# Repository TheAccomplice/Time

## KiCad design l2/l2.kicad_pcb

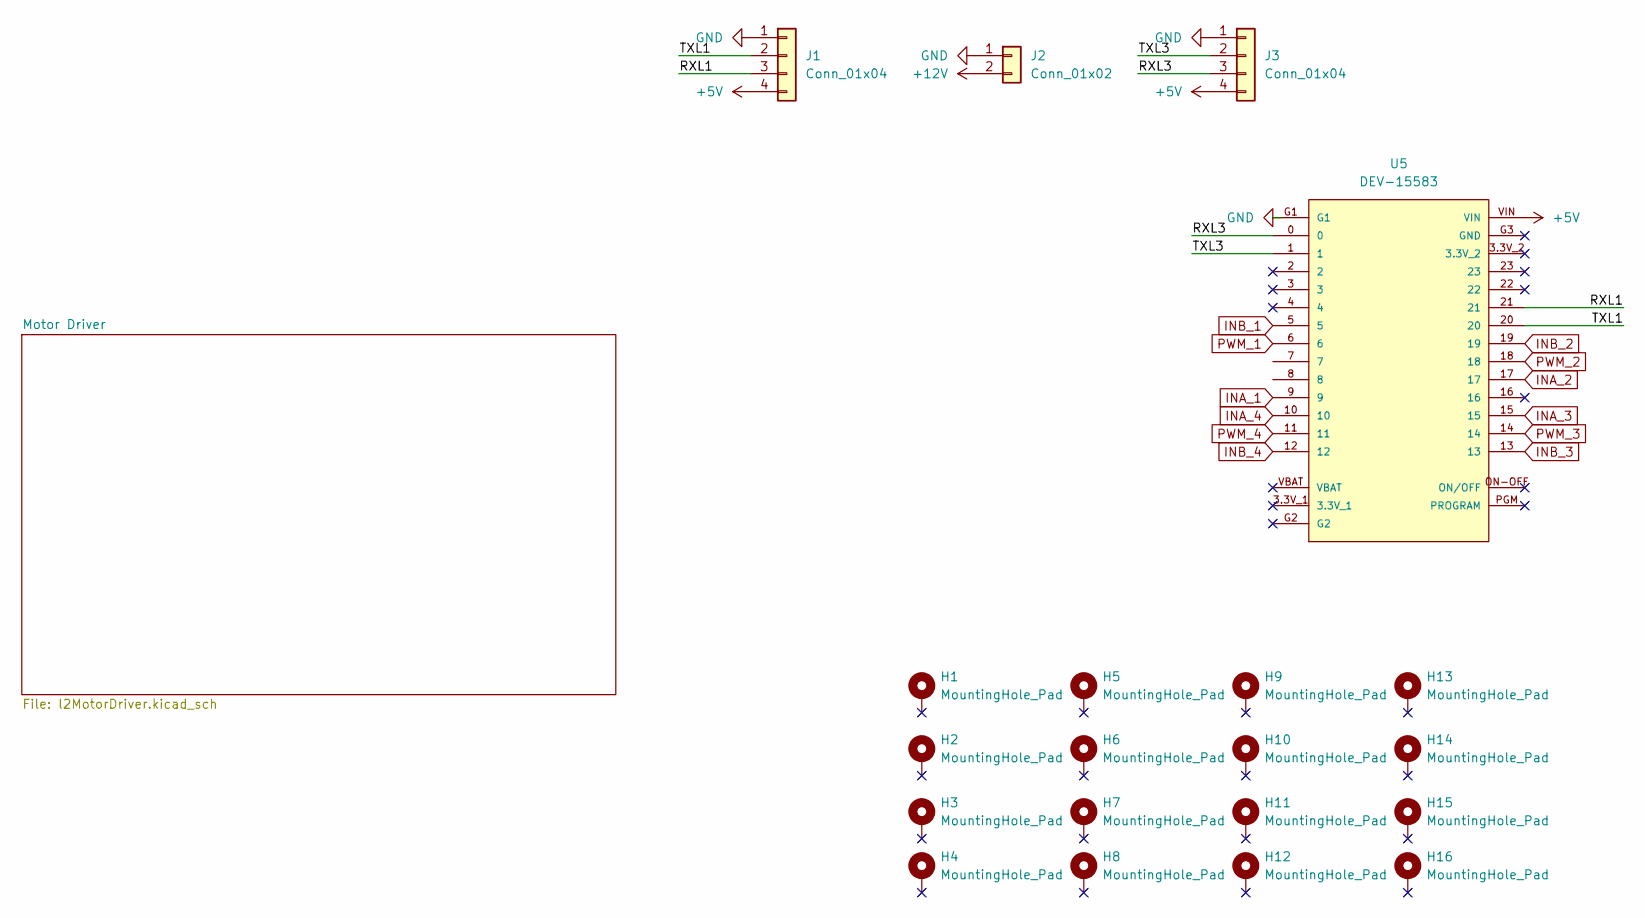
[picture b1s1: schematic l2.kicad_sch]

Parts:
H1, H2, H3, H4, H5, H6, H7, H8, H9, H10, H11, H12, H13, H14, H15, H16: MountingHole_Pad; MountingHole_3.2mm_M3_Pad_Via
J1, J3: Conn_01x04; JST_XH_B4B-XH-AM_1x04_P2.50mm_Vertical
J2: Conn_01x02; AMASS_XT60-M_1x02_P7.20mm_Vertical
U5: DEV-15583; MODULE_DEV-15583

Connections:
+5V: J1.4, J3.4, U5.VIN; also elsewhere on the board
+12V: J2.2; also elsewhere on the board
/RXL1: J1.3, U5.21
/RXL3: J3.3, U5.0
/TXL1: J1.2, U5.20
/TXL3: J3.2, U5.1
GND: J1.1, J2.1, J3.1, U5.G1; also elsewhere on the board
INA_1: U5.9; also elsewhere on the board
INA_2: U5.17; also elsewhere on the board
INA_3: U5.15; also elsewhere on the board
INA_4: U5.10; also elsewhere on the board
INB_1: U5.5; also elsewhere on the board
INB_2: U5.19; also elsewhere on the board
INB_3: U5.13; also elsewhere on the board
INB_4: U5.12; also elsewhere on the board
PWM_1: U5.6; also elsewhere on the board
PWM_2: U5.18; also elsewhere on the board
PWM_3: U5.14; also elsewhere on the board
PWM_4: U5.11; also elsewhere on the board

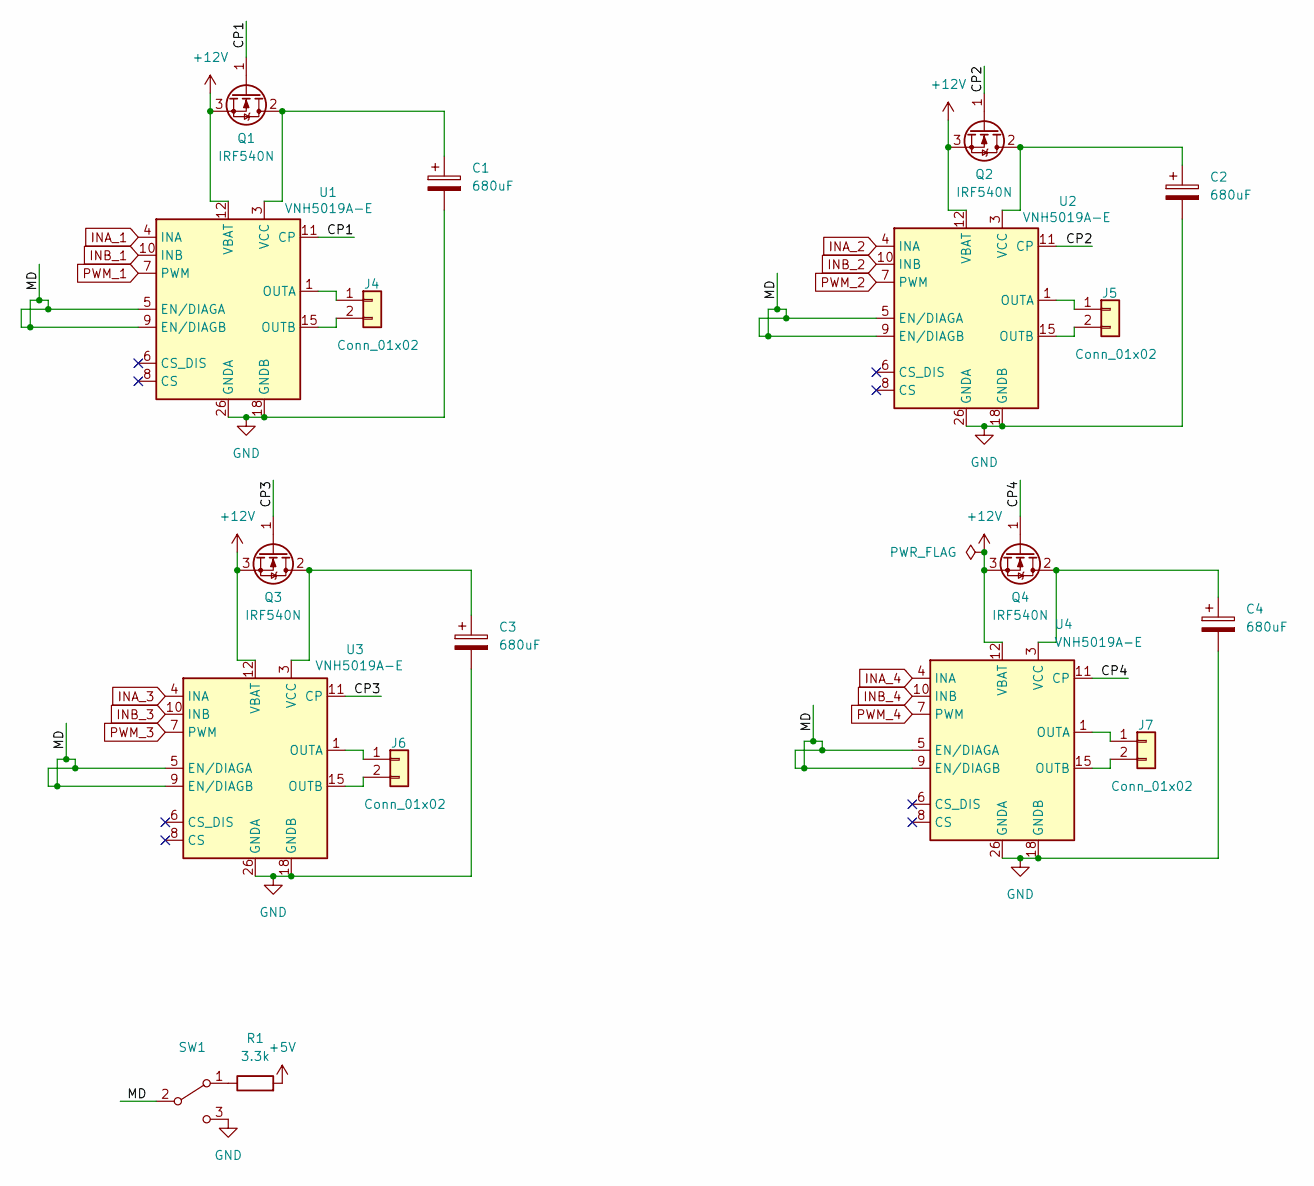
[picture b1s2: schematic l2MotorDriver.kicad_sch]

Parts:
C1, C2, C3, C4: 680uF; CP_Radial_D8.0mm_P3.50mm
J4, J5, J6, J7: Conn_01x02; AMASS_XT30UPB-F_1x02_P5.0mm_Vertical
Q1, Q2, Q3, Q4: IRF540N; TO-220-3_Vertical
R1: 3.3k; R_0603_1608Metric_Pad0.98x0.95mm_HandSolder
SW1: SW_SPDT; JST_XH_B3B-XH-AM_1x03_P2.50mm_Vertical
U1, U2, U3, U4: VNH5019A-E; VNH5019A-E_SO-30

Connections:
+5V: R1.2; also elsewhere on the board
+12V: Q1.3 (S), Q2.3 (S), Q3.3 (S), Q4.3 (S), U1.12 (VBAT), U2.12 (VBAT), U3.12 (VBAT), U4.12 (VBAT); also elsewhere on the board
/Motor Driver/CP1: Q1.1 (G), U1.11 (CP)
/Motor Driver/CP2: Q2.1 (G), U2.11 (CP)
/Motor Driver/CP3: Q3.1 (G), U3.11 (CP)
/Motor Driver/CP4: Q4.1 (G), U4.11 (CP)
/Motor Driver/MD: SW1.2 (B), U1.5 (EN/DIAGA), U1.9 (EN/DIAGB), U2.5 (EN/DIAGA), U2.9 (EN/DIAGB), U3.5 (EN/DIAGA), U3.9 (EN/DIAGB), U4.5 (EN/DIAGA), U4.9 (EN/DIAGB)
GND: C1.2, C2.2, C3.2, C4.2, SW1.3 (C), U1.18 (GNDB), U1.19 (GNDB), U1.20 (GNDB), U1.26 (GNDA), U1.27 (GNDA), U1.28 (GNDA), U2.18 (GNDB), U2.19 (GNDB), U2.20 (GNDB), U2.26 (GNDA), U2.27 (GNDA), U2.28 (GNDA), U3.18 (GNDB), U3.19 (GNDB), U3.20 (GNDB), U3.26 (GNDA), U3.27 (GNDA), U3.28 (GNDA), U4.18 (GNDB), U4.19 (GNDB), U4.20 (GNDB), U4.26 (GNDA), U4.27 (GNDA), U4.28 (GNDA); also elsewhere on the board
INA_1: U1.4 (INA); also elsewhere on the board
INA_2: U2.4 (INA); also elsewhere on the board
INA_3: U3.4 (INA); also elsewhere on the board
INA_4: U4.4 (INA); also elsewhere on the board
INB_1: U1.10 (INB); also elsewhere on the board
INB_2: U2.10 (INB); also elsewhere on the board
INB_3: U3.10 (INB); also elsewhere on the board
INB_4: U4.10 (INB); also elsewhere on the board
unnamed: J4.1, U1.1 (OUTA), U1.25 (OUTA), U1.30 (OUTA), U1.33 (OUTA)
unnamed: J4.2, U1.15 (OUTB), U1.16 (OUTB), U1.21 (OUTB), U1.32 (OUTB)
unnamed: J5.1, U2.1 (OUTA), U2.25 (OUTA), U2.30 (OUTA), U2.33 (OUTA)
unnamed: J5.2, U2.15 (OUTB), U2.16 (OUTB), U2.21 (OUTB), U2.32 (OUTB)
unnamed: J6.1, U3.1 (OUTA), U3.25 (OUTA), U3.30 (OUTA), U3.33 (OUTA)
unnamed: J6.2, U3.15 (OUTB), U3.16 (OUTB), U3.21 (OUTB), U3.32 (OUTB)
unnamed: J7.1, U4.1 (OUTA), U4.25 (OUTA), U4.30 (OUTA), U4.33 (OUTA)
unnamed: J7.2, U4.15 (OUTB), U4.16 (OUTB), U4.21 (OUTB), U4.32 (OUTB)
unnamed: C1.1, Q1.2 (D), U1.3 (VCC), U1.13 (VCC), U1.23 (VCC), U1.31 (VCC)
unnamed: C2.1, Q2.2 (D), U2.3 (VCC), U2.13 (VCC), U2.23 (VCC), U2.31 (VCC)
unnamed: C3.1, Q3.2 (D), U3.3 (VCC), U3.13 (VCC), U3.23 (VCC), U3.31 (VCC)
unnamed: C4.1, Q4.2 (D), U4.3 (VCC), U4.13 (VCC), U4.23 (VCC), U4.31 (VCC)
unnamed: R1.1, SW1.1 (A)
PWM_1: U1.7 (PWM); also elsewhere on the board
PWM_2: U2.7 (PWM); also elsewhere on the board
PWM_3: U3.7 (PWM); also elsewhere on the board
PWM_4: U4.7 (PWM); also elsewhere on the board

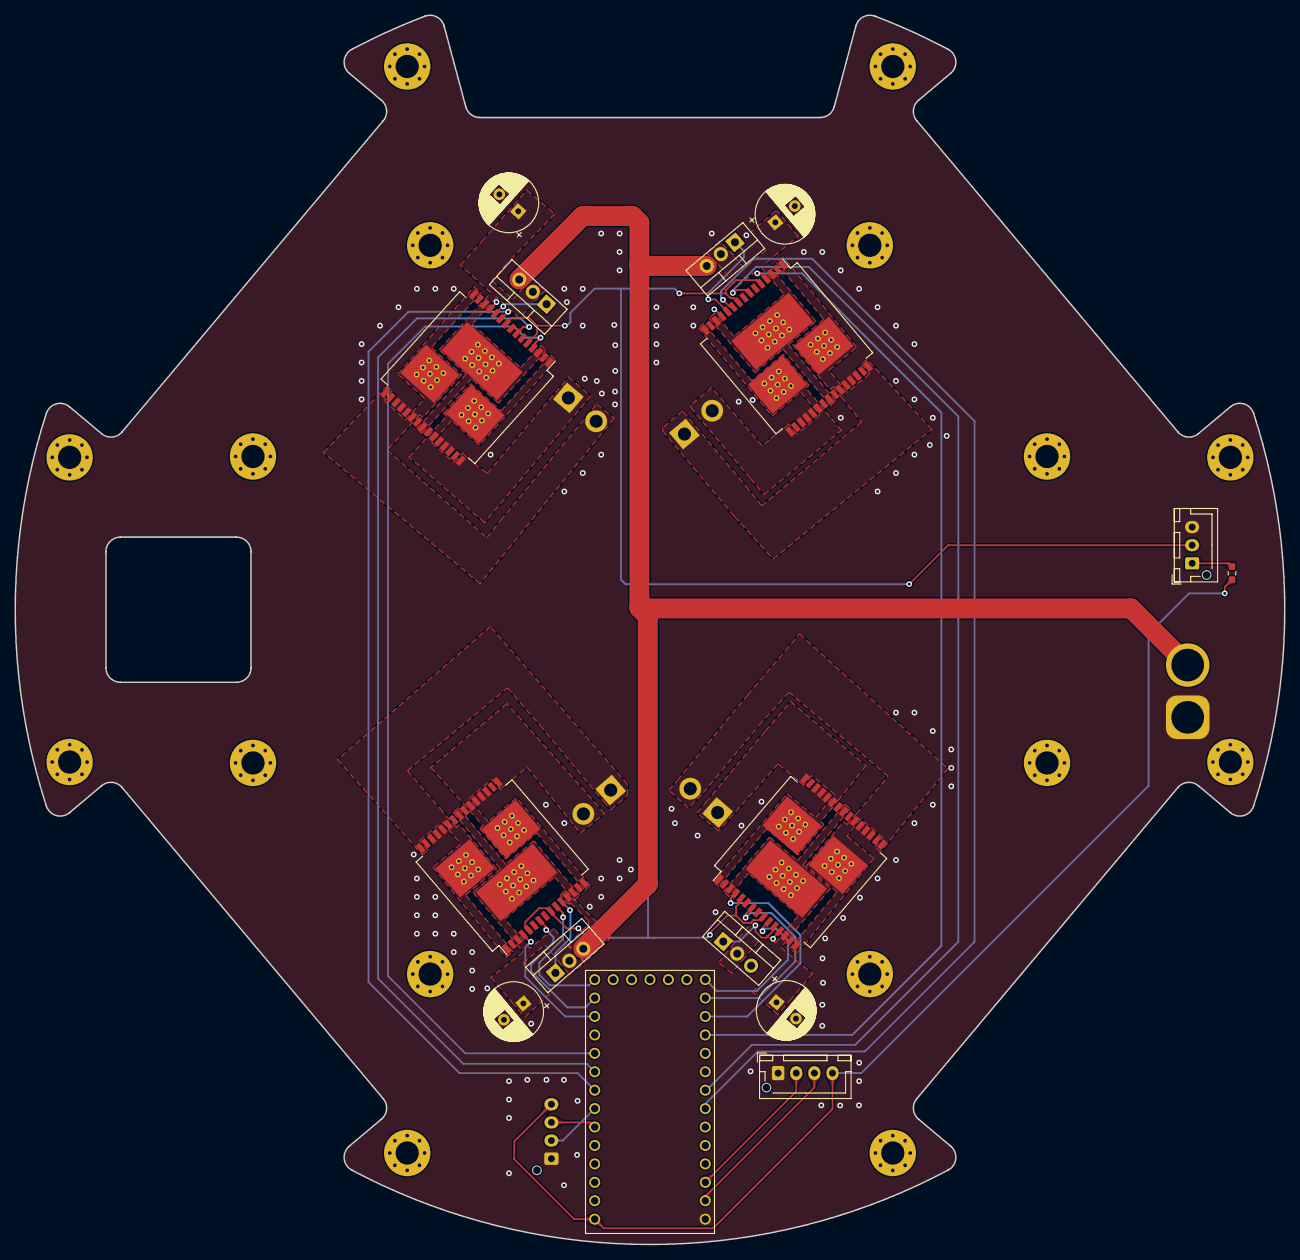
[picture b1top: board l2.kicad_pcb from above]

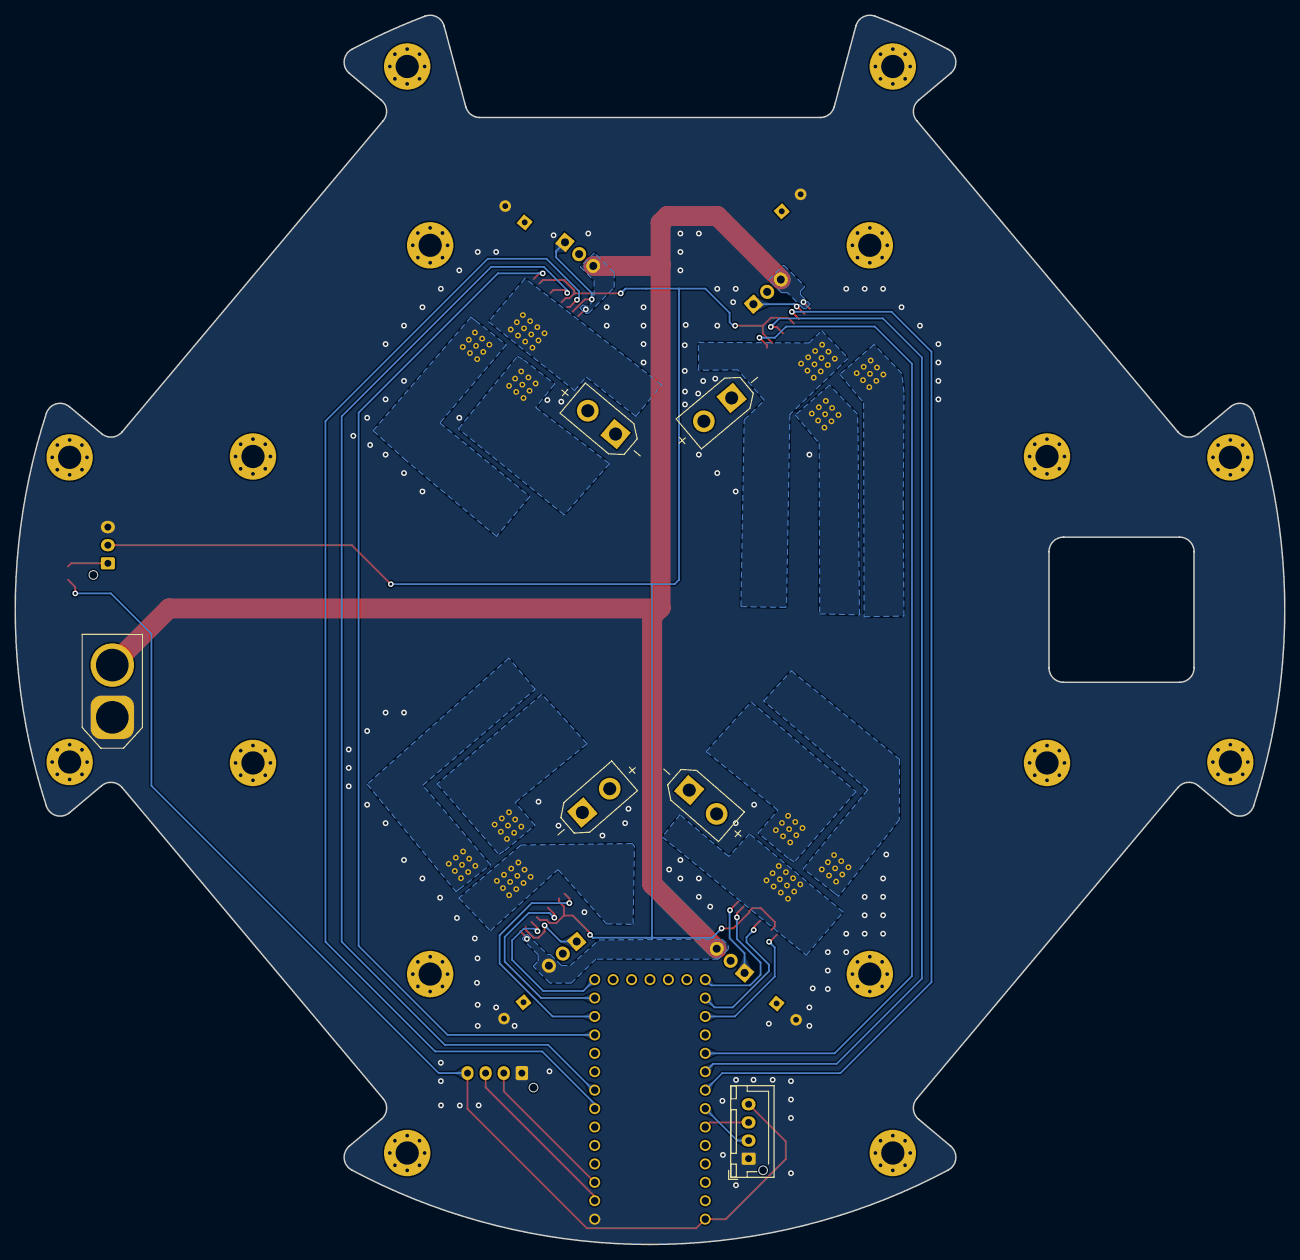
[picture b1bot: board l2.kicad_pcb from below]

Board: 2 copper layers, 175.0 x 169.4 mm, 38 parts (6 on the bottom side), 37 nets.

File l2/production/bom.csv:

Designator,Footprint,Quantity,Value,LCSC Part #
"C1, C2, C3, C4",CP_Radial_D8.0mm_P3.50mm,4,680uF,
"H1, H10, H11, H12, H13, H14, H15, H16, H2, H3, H4, H5, H6, H7, H8, H9",MountingHole_3.2mm_M3_Pad_Via,16,MountingHole_Pad,
"J1, J3",JST_XH_B4B-XH-AM_1x04_P2.50mm_Vertical,2,Conn_01x04,
J2,AMASS_XT60-M_1x02_P7.20mm_Vertical,1,Conn_01x02,
"J4, J5, J6, J7",AMASS_XT30UPB-F_1x02_P5.0mm_Vertical,4,Conn_01x02,
"Q1, Q2, Q3, Q4",TO-220-3_Vertical,4,IRF540N,
R1,0603,1,3.3k,
SW1,JST_XH_B3B-XH-AM_1x03_P2.50mm_Vertical,1,SW_SPDT,
"U1, U2, U3, U4",VNH5019A-E_SO-30,4,VNH5019A-E,
U5,MODULE_DEV-15583,1,DEV-15583,

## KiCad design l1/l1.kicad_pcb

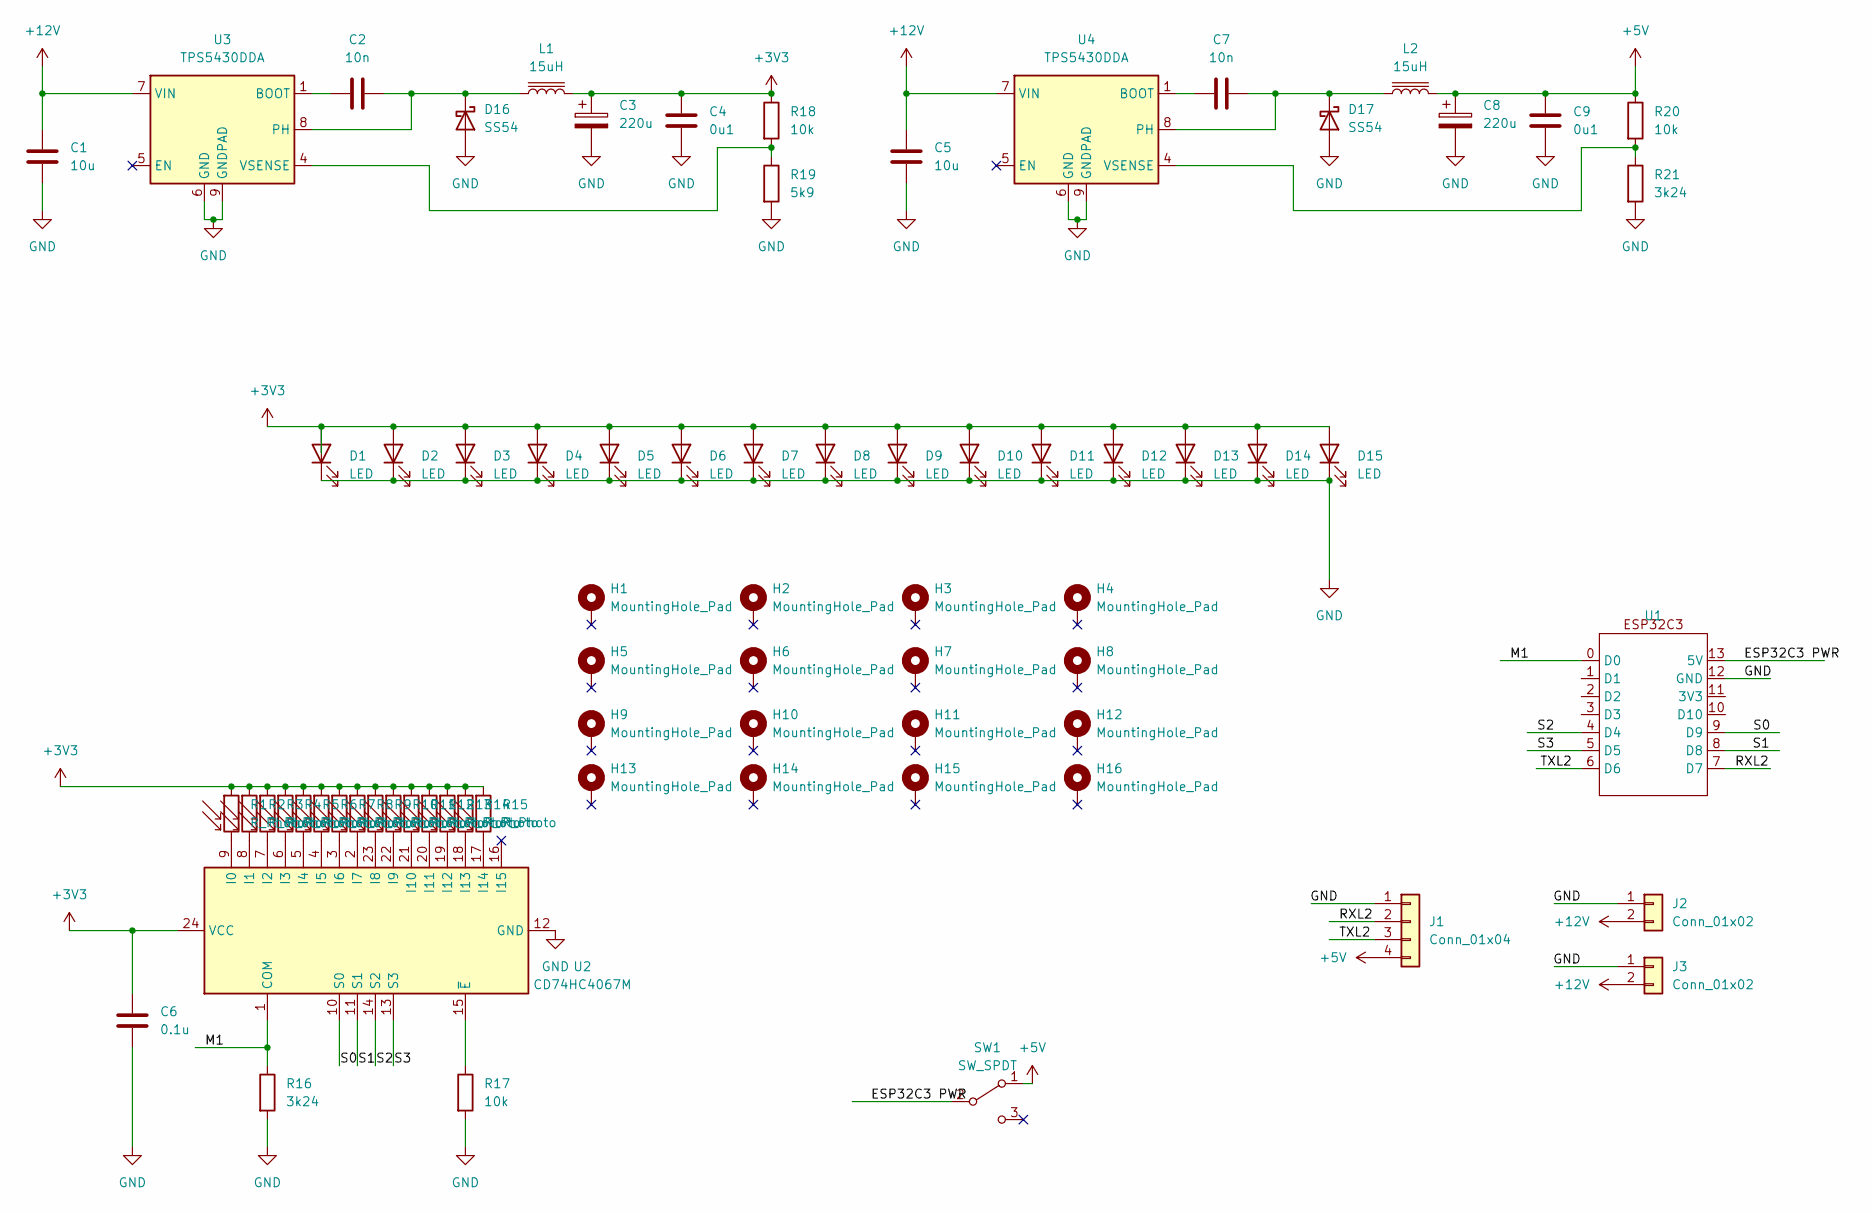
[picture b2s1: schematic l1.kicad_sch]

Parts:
C1, C5: 10u; C_0603_1608Metric_Pad1.08x0.95mm_HandSolder
C2, C7: 10n; C_0603_1608Metric_Pad1.08x0.95mm_HandSolder
C3, C8: 220u; CP_EIA-7343-15_Kemet-W_Pad2.25x2.55mm_HandSolder
C4, C9: 0u1; C_0603_1608Metric_Pad1.08x0.95mm_HandSolder
C6: 0.1u; C_0603_1608Metric_Pad1.08x0.95mm_HandSolder
D1, D2, D3, D4, D5, D6, D7, D8, D9, D10, D11, D12, D13, D14, D15: LED; LED_PLCC_2835_Handsoldering
D16, D17: SS54; D_SMA_Handsoldering
H1, H2, H3, H4, H5, H6, H7, H8, H9, H10, H11, H12, H13, H14, H15, H16: MountingHole_Pad; MountingHole_3.2mm_M3_Pad_Via
J1: Conn_01x04; JST_XH_B4B-XH-AM_1x04_P2.50mm_Vertical
J2, J3: Conn_01x02; AMASS_XT60-M_1x02_P7.20mm_Vertical
L1, L2: 15uH; L_Bourns_SRR1208_12.7x12.7mm
R1, R2, R3, R4, R5, R6, R7, R8, R9, R10, R11, R12, R13, R14, R15: R_Photo; LED_0603_1608Metric
R16, R21: 3k24; R_0603_1608Metric_Pad0.98x0.95mm_HandSolder
R17, R18, R20: 10k; R_0603_1608Metric_Pad0.98x0.95mm_HandSolder
R19: 5k9; R_0603_1608Metric_Pad0.98x0.95mm_HandSolder
SW1: SW_SPDT; SS12D00G3-2.5mm
U1: xiao-esp32c3
U2: CD74HC4067M; SOIC-24W_7.5x15.4mm_P1.27mm
U3, U4: TPS5430DDA; TI_SO-PowerPAD-8_ThermalVias

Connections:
+3V3: C3.1, C4.1, C6.1, D1.2 (A), D2.2 (A), D3.2 (A), D4.2 (A), D5.2 (A), D6.2 (A), D7.2 (A), D8.2 (A), D9.2 (A), D10.2 (A), D11.2 (A), D12.2 (A), D13.2 (A), D14.2 (A), D15.2 (A), L1.2, R1.1, R2.1, R3.1, R4.1, R5.1, R6.1, R7.1, R8.1, R9.1, R10.1, R11.1, R12.1, R13.1, R14.1, R15.1, R18.1, U2.24 (VCC)
+5V: C8.1, C9.1, J1.4, L2.2, R20.1, SW1.1 (A)
+12V: C1.1, C5.1, J2.2, J3.2, U3.7 (VIN), U4.7 (VIN)
/ESP32C3 PWR: SW1.2 (B), U1.13 (5V)
/M1: R16.1, U1.0 (D0), U2.1 (COM)
/RXL2: J1.2, U1.7 (D7)
/S0: U1.9 (D9), U2.10 (S0)
/S1: U1.8 (D8), U2.11 (S1)
/S2: U1.4 (D4), U2.14 (S2)
/S3: U1.5 (D5), U2.13 (S3)
/TXL2: J1.3, U1.6 (D6)
GND: C1.2, C3.2, C4.2, C5.2, C6.2, C8.2, C9.2, D1.1 (K), D2.1 (K), D3.1 (K), D4.1 (K), D5.1 (K), D6.1 (K), D7.1 (K), D8.1 (K), D9.1 (K), D10.1 (K), D11.1 (K), D12.1 (K), D13.1 (K), D14.1 (K), D15.1 (K), D16.2 (A), D17.2 (A), J1.1, J2.1, J3.1, R16.2, R17.2, R19.2, R21.2, U1.12 (GND), U2.12 (GND), U3.6 (GND), U3.9 (GNDPAD), U4.6 (GND), U4.9 (GNDPAD)
unnamed: C2.2, D16.1 (K), L1.1, U3.8 (PH)
unnamed: C7.2, D17.1 (K), L2.1, U4.8 (PH)
unnamed: R1.2, U2.9 (I0)
unnamed: R2.2, U2.8 (I1)
unnamed: R3.2, U2.7 (I2)
unnamed: R4.2, U2.6 (I3)
unnamed: R5.2, U2.5 (I4)
unnamed: R6.2, U2.4 (I5)
unnamed: R7.2, U2.3 (I6)
unnamed: R8.2, U2.2 (I7)
unnamed: R9.2, U2.23 (I8)
unnamed: R10.2, U2.22 (I9)
unnamed: R11.2, U2.21 (I10)
unnamed: R12.2, U2.20 (I11)
unnamed: R13.2, U2.19 (I12)
unnamed: R14.2, U2.18 (I13)
unnamed: R15.2, U2.17 (I14)
unnamed: R17.1, U2.15 (~E)
unnamed: C2.1, U3.1 (BOOT)
unnamed: R18.2, R19.1, U3.4 (VSENSE)
unnamed: C7.1, U4.1 (BOOT)
unnamed: R20.2, R21.1, U4.4 (VSENSE)

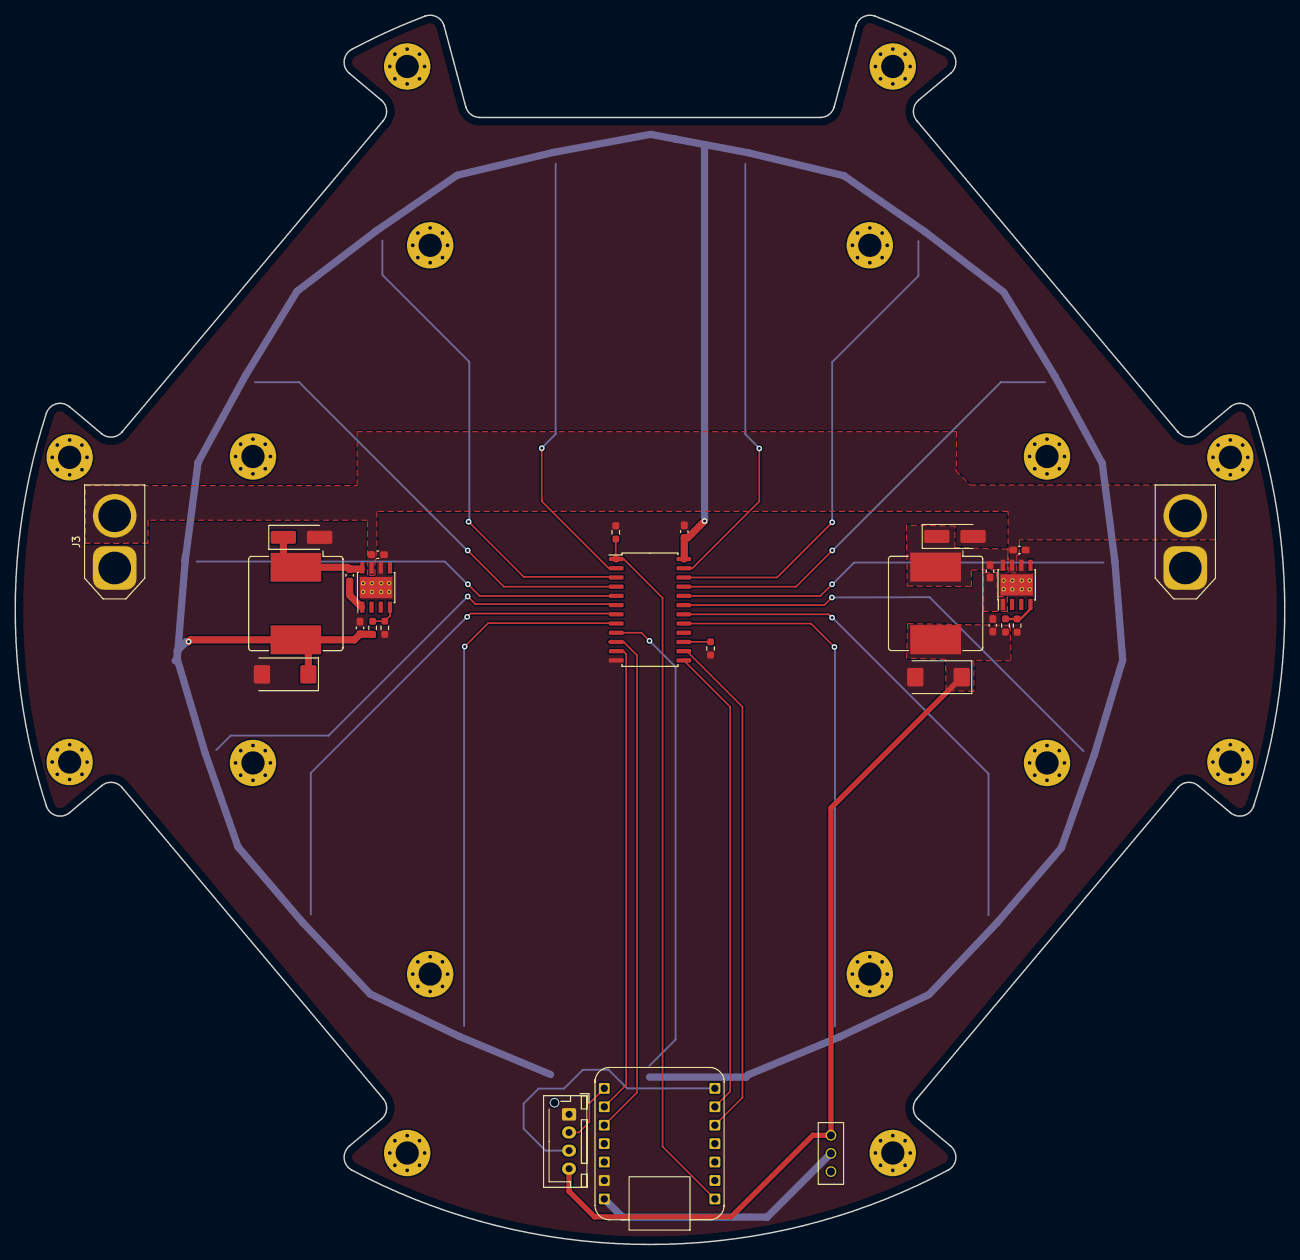
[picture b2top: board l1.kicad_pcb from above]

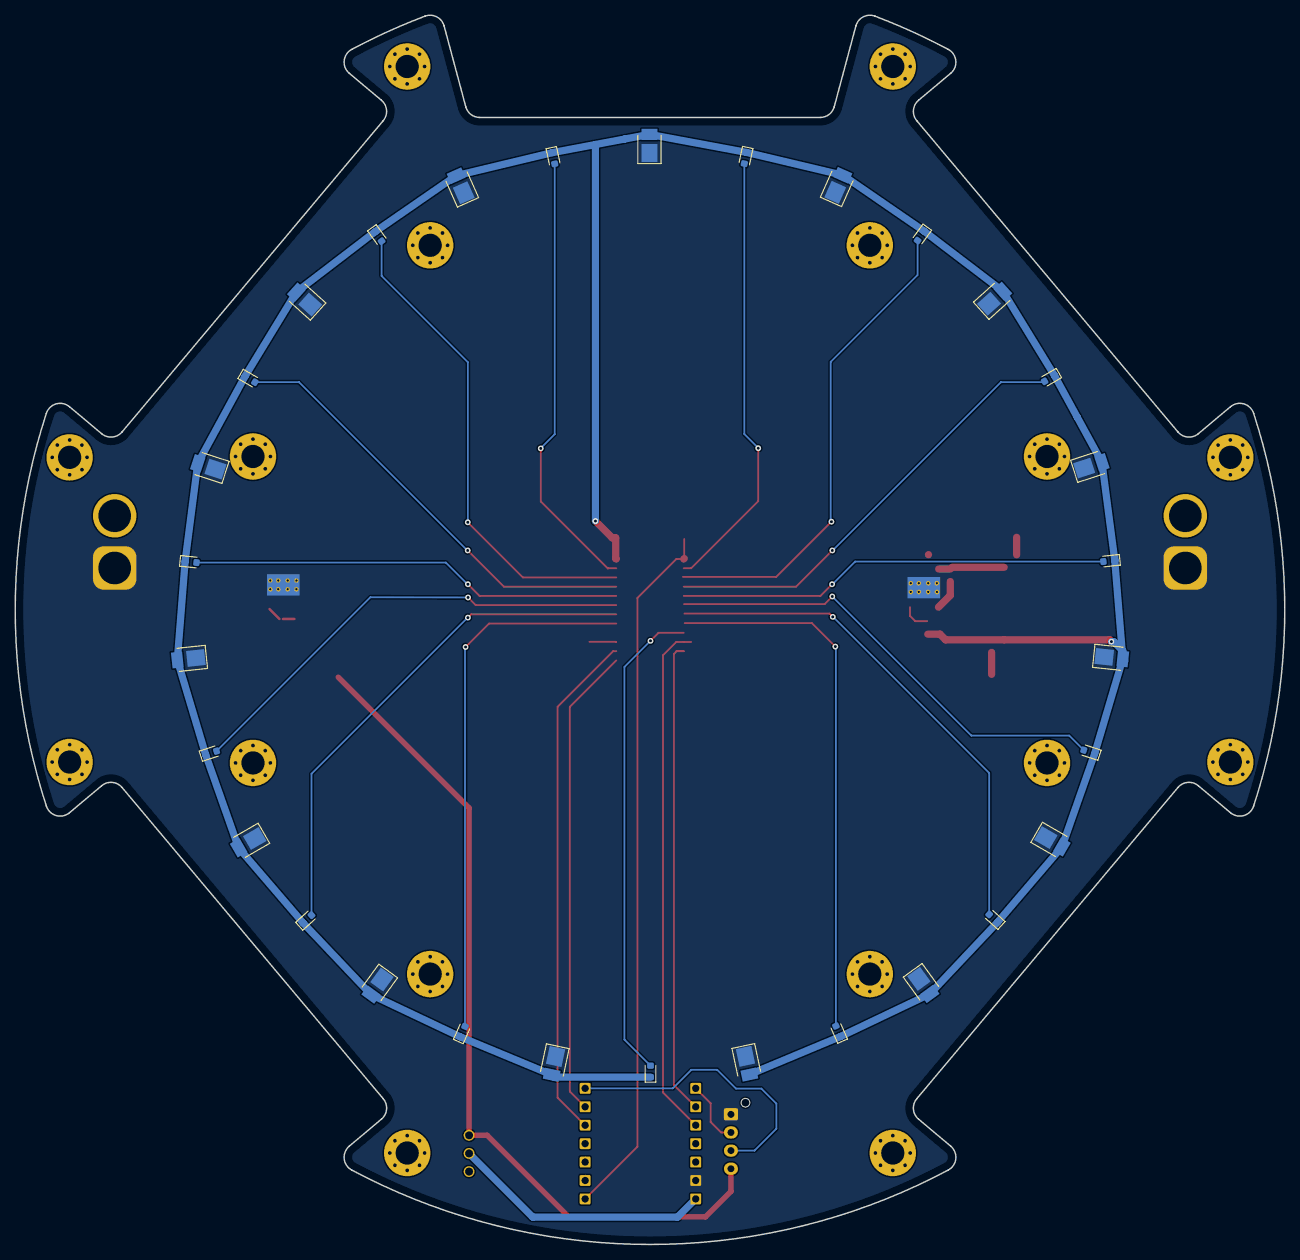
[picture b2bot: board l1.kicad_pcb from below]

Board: 2 copper layers, 175.0 x 169.4 mm, 73 parts (30 on the bottom side), 34 nets.

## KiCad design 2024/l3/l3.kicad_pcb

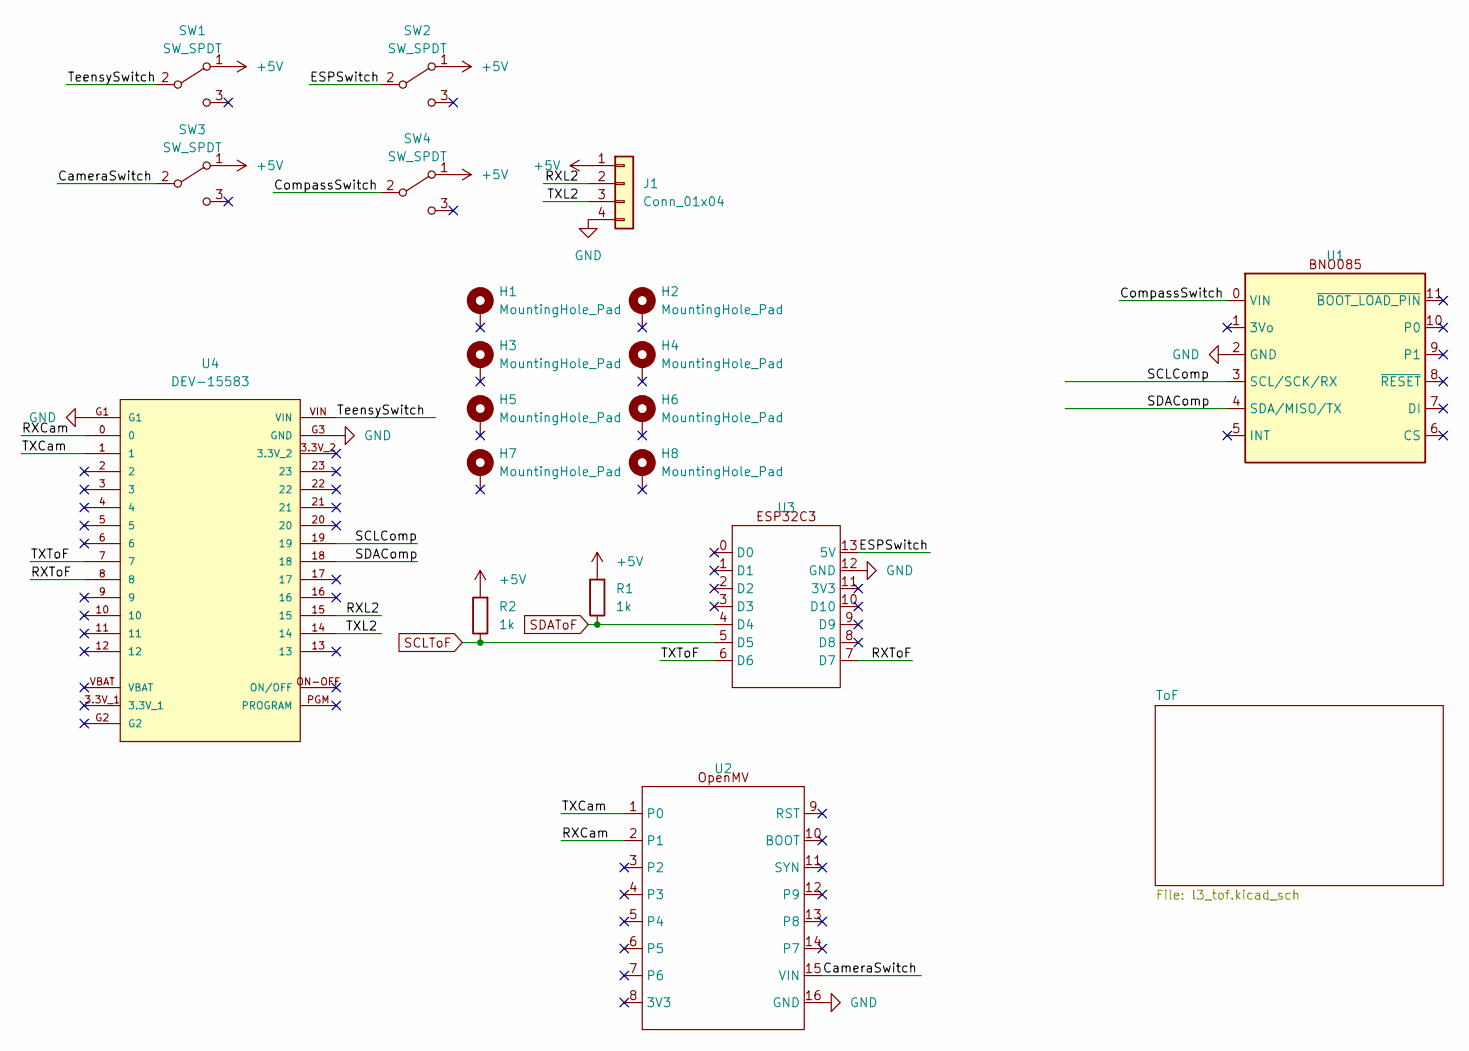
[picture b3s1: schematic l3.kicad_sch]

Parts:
H1, H2, H3, H4, H5, H6, H7, H8: MountingHole_Pad; MountingHole_3.2mm_M3_Pad_Via
J1: Conn_01x04; JST_XH_B4B-XH-AM_1x04_P2.50mm_Vertical
R1, R2: 1k; R_0603_1608Metric_Pad0.98x0.95mm_HandSolder
SW1, SW2, SW3, SW4: SW_SPDT; SS12D00G3-2.5mm
U1: BNO085
U2: OpenMV
U3: xiao-esp32c3
U4: DEV-15583; MODULE_DEV-15583

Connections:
+5V: J1.1, R1.2, R2.2, SW1.1 (A), SW2.1 (A), SW3.1 (A), SW4.1 (A); also elsewhere on the board
/CameraSwitch: SW3.2 (B), U2.15 (VIN)
/CompassSwitch: SW4.2 (B), U1.0 (VIN)
/ESPSwitch: SW2.2 (B), U3.13 (5V)
/RXCam: U2.2 (P1), U4.0
/RXL2: J1.2, U4.15
/RXToF: U3.7 (D7), U4.8
/SCLComp: U1.3 (SCL/SCK/RX), U4.19
/SDAComp: U1.4 (SDA/MISO/TX), U4.18
/TXCam: U2.1 (P0), U4.1
/TXL2: J1.3, U4.14
/TXToF: U3.6 (D6), U4.7
/TeensySwitch: SW1.2 (B), U4.VIN
GND: J1.4, U1.2 (GND), U2.16 (GND), U3.12 (GND), U4.G1, U4.G3 (GND); also elsewhere on the board
SCLToF: R2.1, U3.5 (D5); also elsewhere on the board
SDAToF: R1.1, U3.4 (D4); also elsewhere on the board

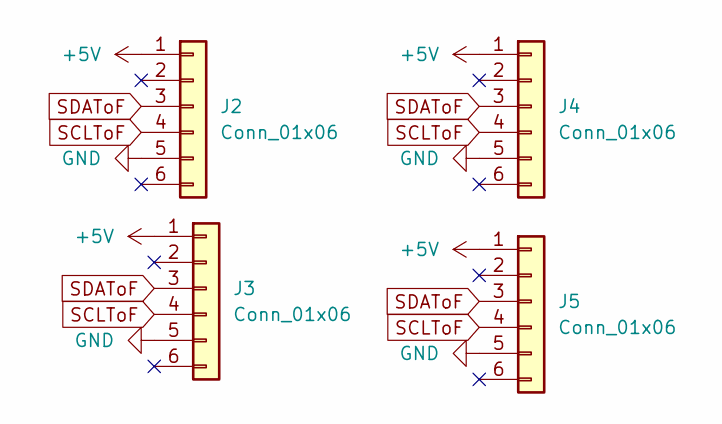
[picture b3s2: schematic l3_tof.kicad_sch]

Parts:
J2, J3, J4, J5: Conn_01x06; PinHeader_1x06_P2.54mm_Vertical

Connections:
+5V: J2.1, J3.1, J4.1, J5.1; also elsewhere on the board
GND: J2.5, J3.5, J4.5, J5.5; also elsewhere on the board
SCLToF: J2.4, J3.4, J4.4, J5.4; also elsewhere on the board
SDAToF: J2.3, J3.3, J4.3, J5.3; also elsewhere on the board

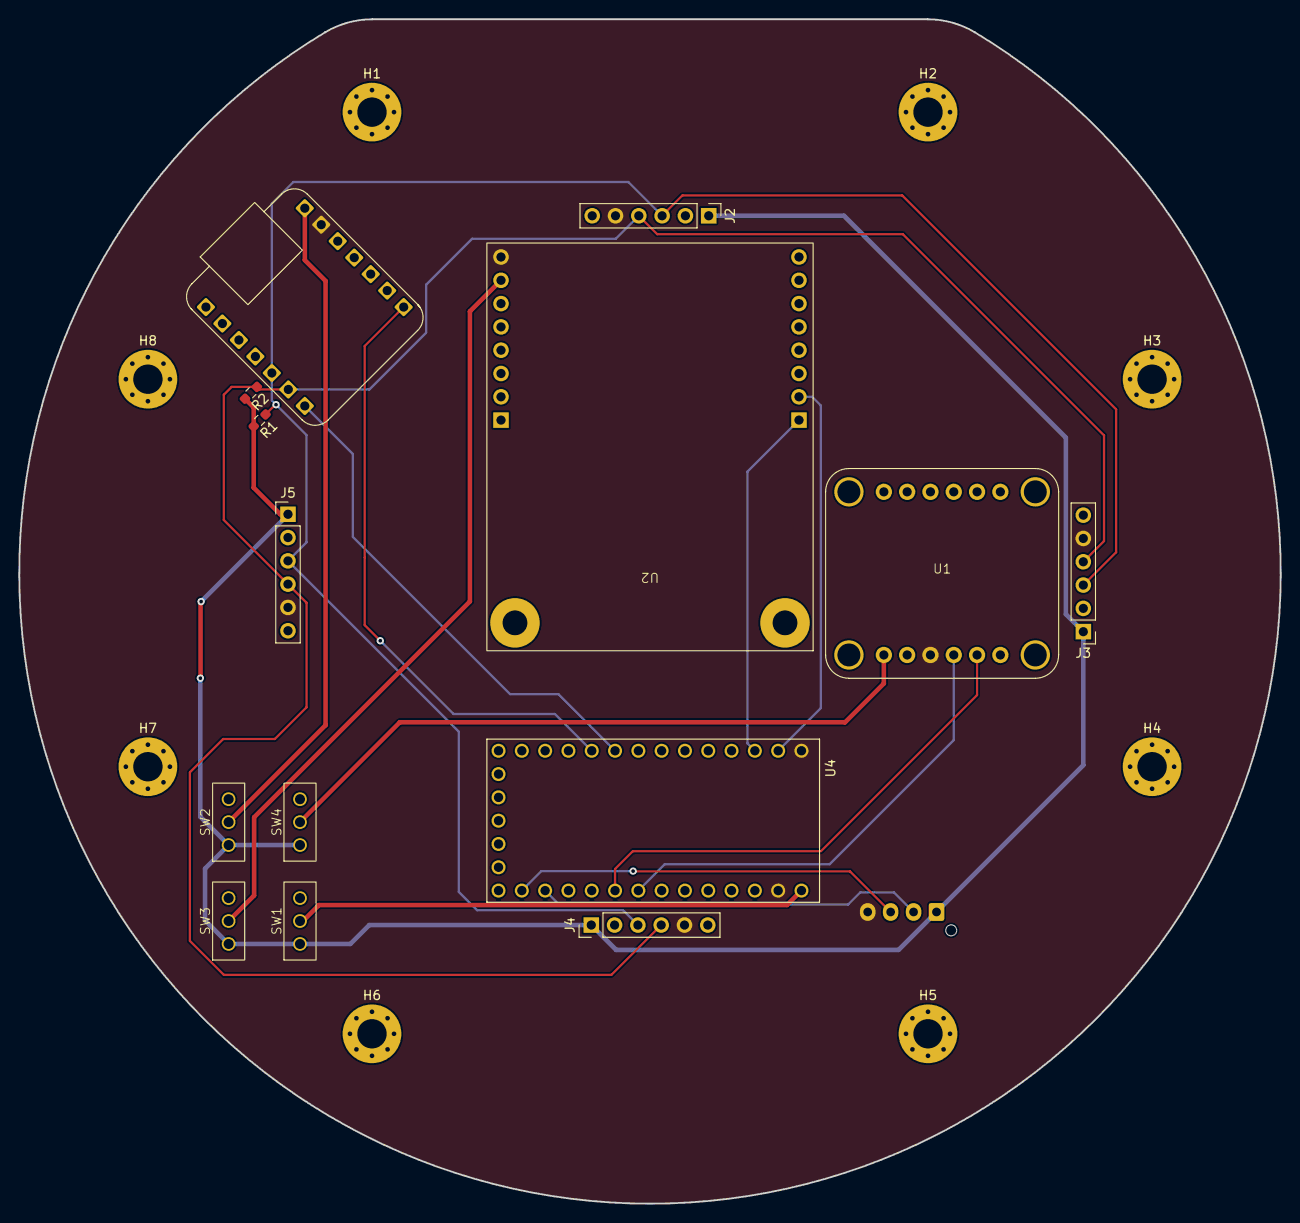
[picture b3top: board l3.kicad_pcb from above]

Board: 2 copper layers, 137.5 x 129.1 mm, 23 parts (1 on the bottom side), 16 nets.

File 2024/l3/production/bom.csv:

Designator,Footprint,Quantity,Value,LCSC Part #
"H1, H2, H3, H4, H5, H6, H7, H8",MountingHole_3.2mm_M3_Pad_Via,8,MountingHole_Pad,
J1,JST_XH_B4B-XH-AM_1x04_P2.50mm_Vertical,1,Conn_01x04,
"J2, J3, J4, J5",PinHeader_1x06_P2.54mm_Vertical,4,Conn_01x06,
"R1, R2",0603,2,1k,
"SW1, SW2, SW3, SW4",SS12D00G3-2.5mm,4,SW_SPDT,
U1,BNO085,1,~,
U2,OpenMV,1,~,
U3,xiao-esp32c3,1,~,
U4,MODULE_DEV-15583,1,DEV-15583,

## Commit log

2024-07-05 Copy Over
2024-07-05 readd trace
2024-07-05 2024 folder
2024-07-05 remove trace test
2024-07-05 replace trace test
2024-07-05 deleted additional
2024-07-05 another test
2024-07-05 new folder
2024-07-05 deleted new folder
2024-07-05 add back trace
2024-07-05 pcb lck removed
2024-07-05 5/7 Final
2024-07-05 5/7 Final2
2024-07-12 PCB_done
    Rearrange traces
2024-07-12 PCB done
2024-07-12 nose
2024-07-13 13/7 final
2024-07-17 17/7 final
2024-07-17 17/7 final 2
2024-07-20 20/7 final
2024-07-26 Motor Driver sch very wonky draft
2024-07-26 26/7 final
2024-07-31 31/7 final
2024-08-02 Refined motor driver schematics
    L2 schematics basically good to go might need final senior's review
2024-08-07 6/8 final
2024-08-07 7/8 part_I
2024-08-07 7/8 part_II
2024-08-07 7/8 final
2024-08-13 13/8 update
2024-08-14 14/8 final
2024-08-16 Fixed motor driver error
    VL53L1X is actual one
2024-08-16 Prev commit was to fix ToF NOT md
2024-08-16 16/8 final
2024-08-21 21/8 final
    about 10% done l2 pcb
2024-08-21 21/8 final2
    still about 10% done l2 pcb
2024-08-28 28/8 final
    resistors for motor driver removed as it was too cumbersome to do the traces and is also completely optional
2024-09-04 4/9 final
    some cursed motor driver routing
2024-09-05 5/9 final
    fixed the problem with motor driver schematics
2024-09-08 edited motor driver pcb
2024-11-24 final 0.9
2024-11-28 final 0.91
    fixed:
    switched analog signal pin on l1 esp32c3 to a0 since a1 not working
    silkscreen is now properly placed
    traces are adjusted on l1
2024-11-29 tf luna
    gerber created for l1 and l2
    l3 changed the tof from vl53l1x to tf luna
2024-11-30 tf luna mount complete
    adjusted a lot of stuff
2024-12-01 final 0.92
    l3 traces going from the switch to vin of components 0.5mm just to be sure
2024-12-11 final 1.0
2025-01-14 v1.090
2025-01-15 v1.091
    fix via over silkscreen
2025-02-05 folder structure rework
2025-02-05 testt
2025-02-05 test again it better work
2025-02-13 v2.0
    l2 l3 done for print
2025-02-14 v2.1
    fixed some stuff
2025-03-26 everything is going perfectly fine
    yes, gaslighting
